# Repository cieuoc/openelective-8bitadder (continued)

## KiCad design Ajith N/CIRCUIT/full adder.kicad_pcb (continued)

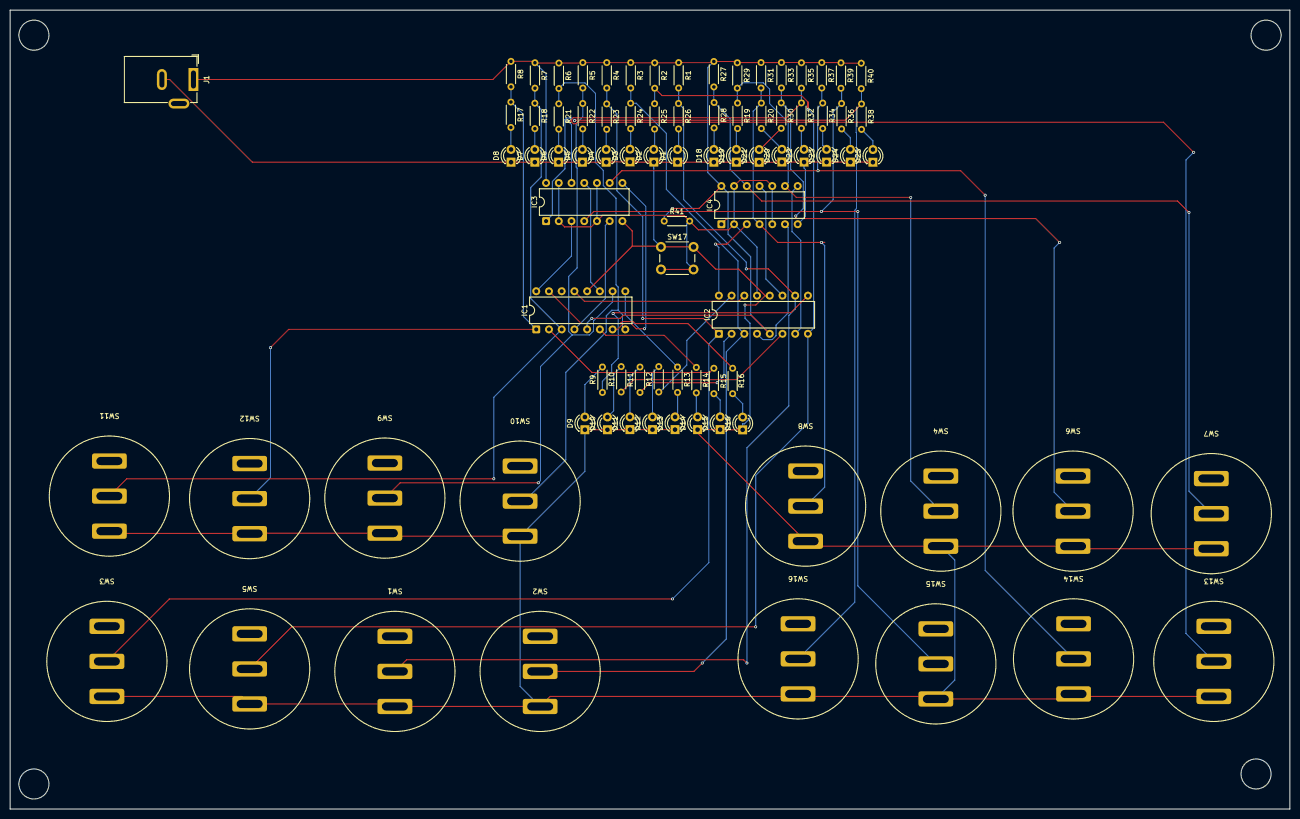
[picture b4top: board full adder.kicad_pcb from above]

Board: 2 copper layers, 255.5 x 159.5 mm, 87 parts (0 on the bottom side), 60 nets.

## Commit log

2025-12-01 Vyshnav commit
2025-12-03 assingment
